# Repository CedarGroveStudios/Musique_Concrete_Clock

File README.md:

# Musique_Concrete_Clock

### RTC-based hybrid cuckoo clock using heirloom sound components, powered by CircuitPython.

Uses a custom Cedar Grove StemmaHost FeatherWing as well as the __CedarGroveStudios/Unit_Converter__ and __CedarGroveStudios/Clock_Builder__ custom CircuitPython libraries.

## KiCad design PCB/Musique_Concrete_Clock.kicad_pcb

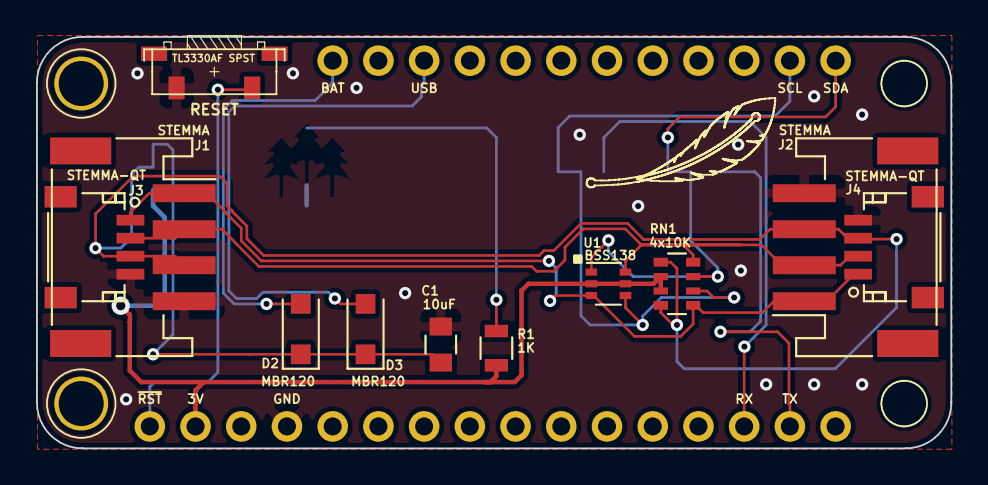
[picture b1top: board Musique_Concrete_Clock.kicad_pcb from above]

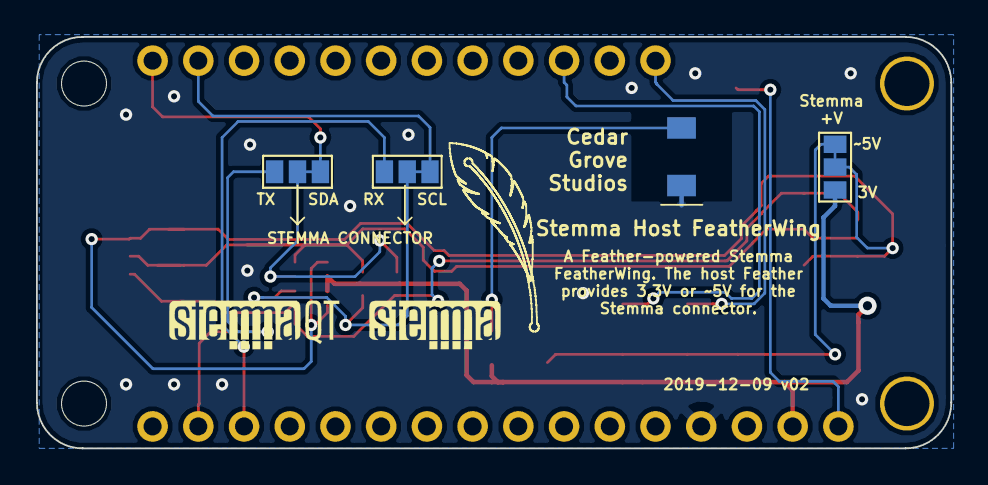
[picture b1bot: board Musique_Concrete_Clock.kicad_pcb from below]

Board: 2 copper layers, 50.8 x 22.9 mm, 16 parts (3 on the bottom side), 13 nets.

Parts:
C1: 10uF; C_0805
D1: GRN; Cedar_Grove_logo_lighted
D2, D3: MBR120; D_SOD-123F
J1, J2: STEMMA; JST_PH_S4B-PH-SM4-TB_04x2.00mm_Angled
J3, J4: STEMMA-QT; JST_SH_SM04B-SRSS-TB_04x1.00mm_Angled
JMP1: SCL_RX; GS3
JMP2: SDA_TX; GS3
JMP3: STEMMA_TYPE; GS3
M1: Feather_M4_Express; Adafruit_Feather_M4_Express_bare
R1: 1K; R_0805
RN1: 4x10K; R_Array_Convex_4x0603
SW1: RESET; TL3330AF_SPST_BUTTON_RT-ANGLE_7.8mm_2.5mm_2.5mm
U1: BSS138; SOT-363_SC-70-6

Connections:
+3V3: JMP3.1, M1.2, R1.1, RN1.2, RN1.3, U1.2, U1.5
/+V: C1.1, D2.1, D3.1, J1.3, J2.3, J3.3, J4.3, JMP3.2, JMP3.3, RN1.1, RN1.4
/BAT: D2.2, M1.17
/RX: JMP1.3, M1.14
/SCL: JMP1.1, JMP1.2, M1.27, RN1.6, U1.4
/SDA: JMP2.1, JMP2.2, M1.28, RN1.7, U1.1
/STEMMA_SCL: J1.1, J2.1, J3.1, J4.1, RN1.5, U1.3
/STEMMA_SDA: J1.2, J2.2, J3.2, J4.2, RN1.8, U1.6
/TX: JMP2.3, M1.15
/USB: D3.2, M1.19
/~RST: M1.1, SW1.2
GND: C1.2, D1.1, J1.4, J2.4, J3.4, J4.4, M1.4, SW1.1
unnamed: D1.2, R1.2

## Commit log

2020-06-09 initial repo load
2020-06-14 update latest code
2020-06-15 update photos
2020-06-19 update main code
